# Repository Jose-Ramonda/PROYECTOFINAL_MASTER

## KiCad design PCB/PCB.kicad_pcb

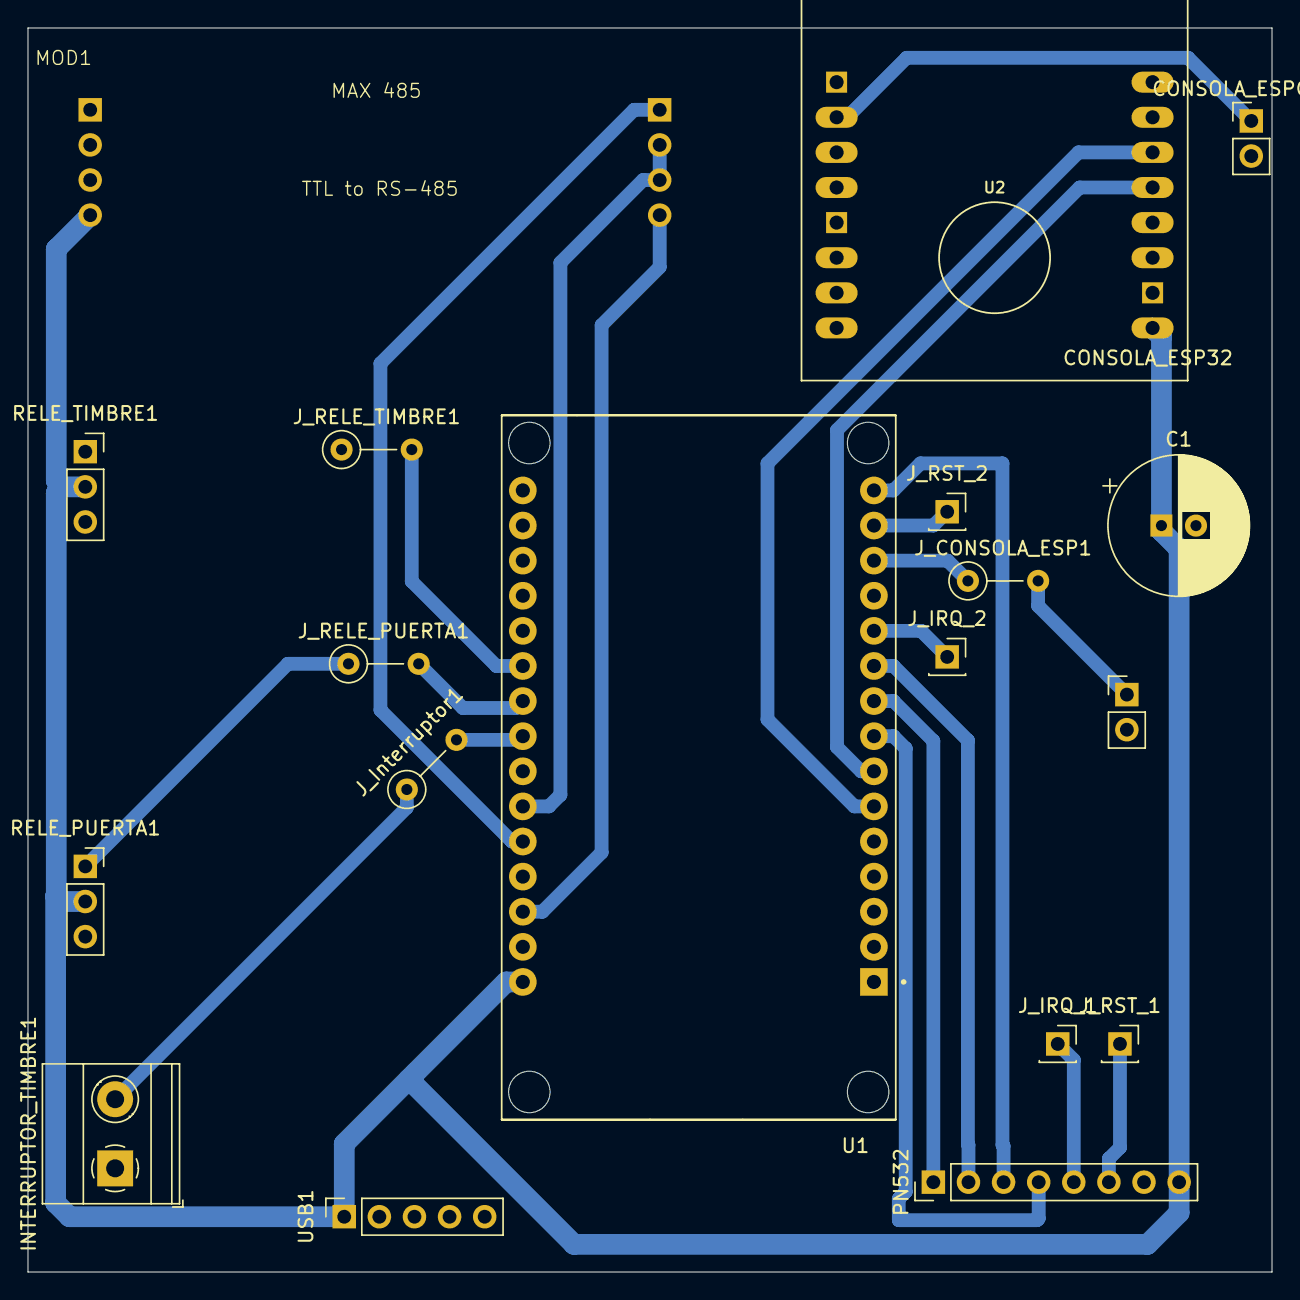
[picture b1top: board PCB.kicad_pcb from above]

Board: 2 copper layers, 90.0 x 90.0 mm, 19 parts (0 on the bottom side), 24 nets.

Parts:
C1: C_Polarized; CP_Radial_D10.0mm_P2.50mm
CONSOLA_ESP32: Conn_01x02; PinHeader_1x02_P2.54mm_Vertical
CONSOLA_ESPCAM1: Conn_01x02; PinHeader_1x02_P2.54mm_Vertical
INTERRUPTOR_TIMBRE1: Conn_01x02; TerminalBlock_Phoenix_MKDS-1,5-2_1x02_P5.00mm_Horizontal
J_CONSOLA_ESP1: 0; R_Axial_DIN0207_L6.3mm_D2.5mm_P5.08mm_Vertical
J_IRQ_1, J_IRQ_2: Conn_01x01_Socket; PinSocket_1x01_P2.54mm_Vertical
J_Interruptor1: 0; R_Axial_DIN0207_L6.3mm_D2.5mm_P5.08mm_Vertical
J_RELE_PUERTA1: 0; R_Axial_DIN0207_L6.3mm_D2.5mm_P5.08mm_Vertical
J_RELE_TIMBRE1: 0; R_Axial_DIN0207_L6.3mm_D2.5mm_P5.08mm_Vertical
J_RST_1, J_RST_2: Conn_01x01_Socket; PinSocket_1x01_P2.54mm_Vertical
MOD1: MAX485
PN532: PN532-Adafruit; PinHeader_1x08_P2.54mm_Vertical
RELE_PUERTA1: Conn_01x03; PinSocket_1x03_P2.54mm_Vertical
RELE_TIMBRE1: Conn_01x03; PinSocket_1x03_P2.54mm_Vertical
U1: ESP32-DEVKIT-V1; MODULE_ESP32_DEVKIT_V1
U2: ESP32-CAM
USB1: Conn_01x05; PinSocket_1x05_P2.54mm_Vertical

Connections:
+5V: C1.1, MOD1.5 (VCC), PN532.8 (5V), RELE_PUERTA1.2, RELE_TIMBRE1.2, U1.30 (VIN), U2.P$9 (5V), USB1.1
/RX2: U1.7 (TX2), U2.P$13 (GPIO15)
/TX2: U1.6 (RX2), U2.P$14 (GPIO14)
GND: C1.2, CONSOLA_ESP32.2, CONSOLA_ESPCAM1.2, INTERRUPTOR_TIMBRE1.1, MOD1.8 (GND), PN532.7 (GND), RELE_PUERTA1.3, RELE_TIMBRE1.3, U1.2 (GND), U1.29 (GND), U2.P$10 (GND@3), USB1.5
unnamed: CONSOLA_ESP32.1, J_CONSOLA_ESP1.2
unnamed: CONSOLA_ESPCAM1.1, U2.P$2 (GPIO1)
unnamed: INTERRUPTOR_TIMBRE1.2, J_Interruptor1.1
unnamed: J_IRQ_1.1, PN532.5 (IRQ)
unnamed: J_IRQ_2.1, U1.11 (D21)
unnamed: J_RST_1.1, PN532.6 (RST)
unnamed: J_RST_2.1, U1.14 (D22)
unnamed: MOD1.2 (DE), MOD1.3 (RE), U1.25 (D27)
unnamed: MOD1.1 (DI), U1.26 (D14)
unnamed: MOD1.4 (RO), U1.28 (D13)
unnamed: PN532.2 (MISO), U1.10 (D19)
unnamed: PN532.3 (MOSI), U1.15 (D23)
unnamed: PN532.1 (SCK), U1.9 (D18)
unnamed: PN532.4 (SS), U1.8 (D5)
unnamed: J_RELE_PUERTA1.1, RELE_PUERTA1.1
unnamed: J_RELE_TIMBRE1.1, RELE_TIMBRE1.1
unnamed: J_Interruptor1.2, U1.23 (D25)
unnamed: J_RELE_TIMBRE1.2, U1.21 (D32)
unnamed: J_RELE_PUERTA1.2, U1.22 (D33)
unnamed: J_CONSOLA_ESP1.1, U1.13 (TX0)

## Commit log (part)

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2026-05-04 Estructura inicial limpia: Informe, Anteproyecto y Bot
2026-05-06 Testing commit windows
2026-05-27 Inicio del informe
2026-06-24 Test
2026-06-24 ASAS
2026-06-28 Creacion de carpeta de PCB Y creación de proyecto
2026-06-29 PCB primera versión de prueba
2026-06-29 Inicio de sección 5 -> firmware
2026-06-30 Adelanto 30-6
